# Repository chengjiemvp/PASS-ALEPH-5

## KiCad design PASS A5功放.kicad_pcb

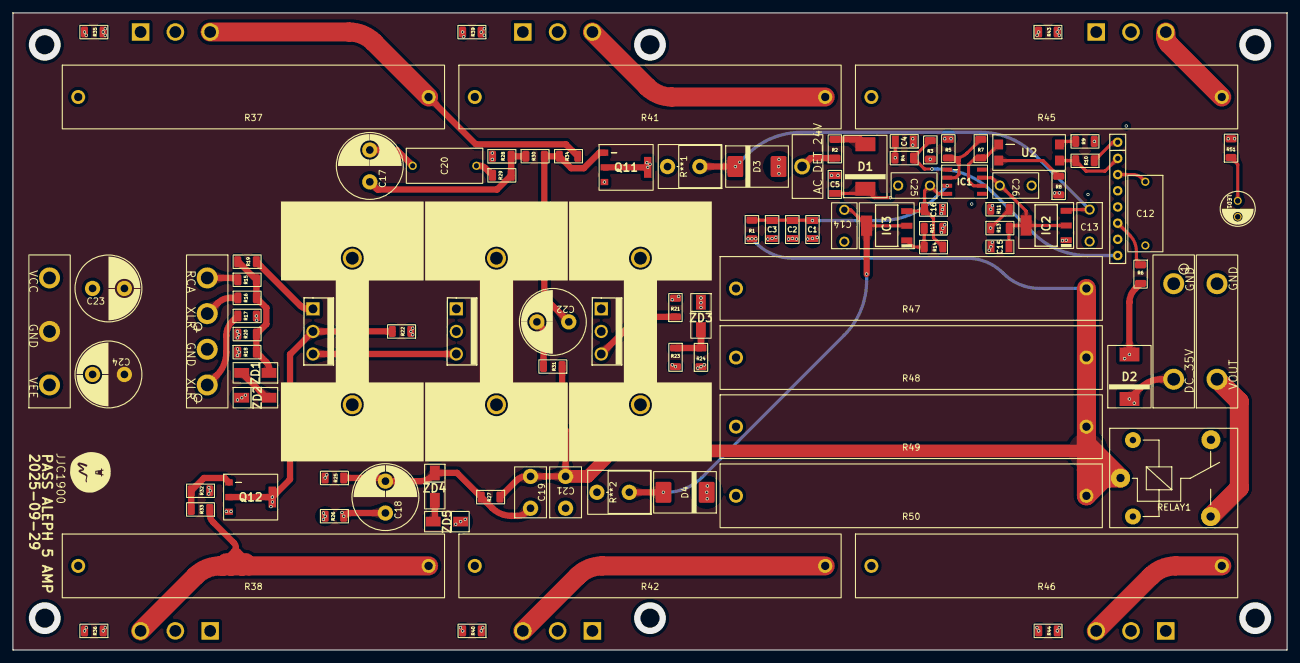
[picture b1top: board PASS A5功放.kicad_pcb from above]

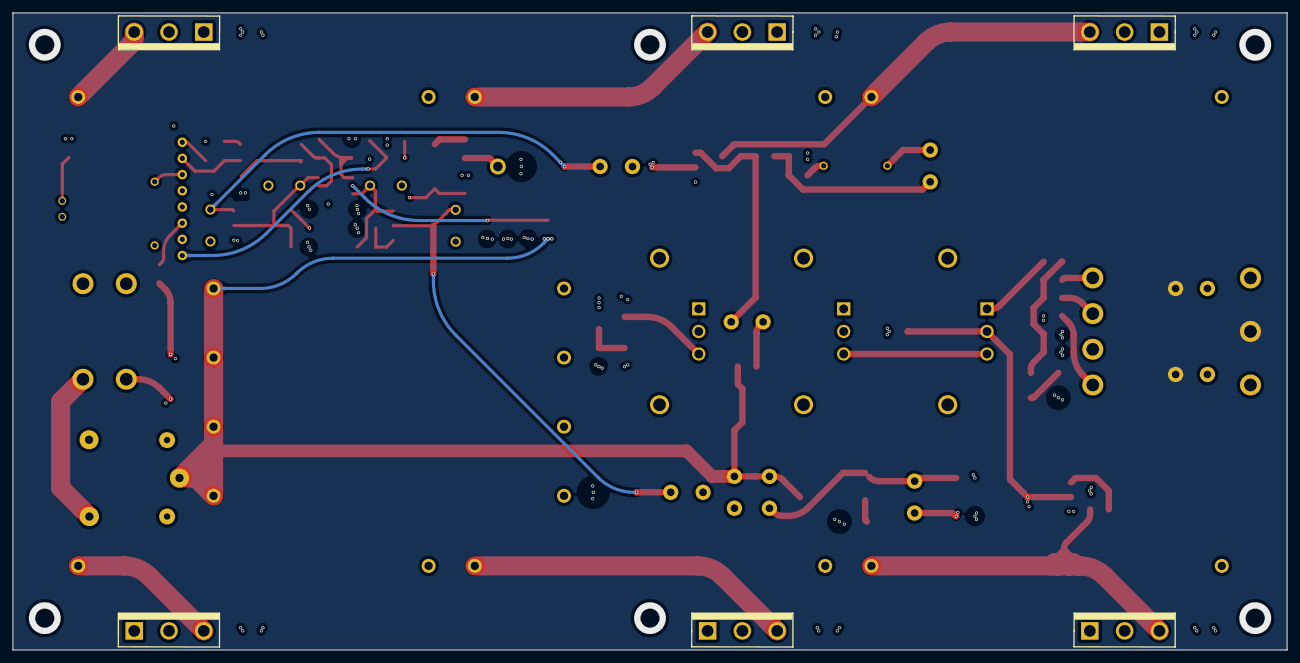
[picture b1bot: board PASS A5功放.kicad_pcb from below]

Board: 6 copper layers, 200.0 x 100.0 mm, 106 parts (6 on the bottom side), 61 nets.

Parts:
C1, C2, C3: 100μ; CGA1206X5R226M350NT
C4: 47μ; C3216X5R1E476MTJ00E
C5: 4.7μ; CL31B475KBHNNNE
C12: 22NF; KP223J2J1001
C13, C14, C25, C26: 0.1μ; MES104J2A-7-50R0
C15, C16: 22μ; CGA1206X5R226M350NT
C17, C18, C22: 220UF; SPZ1HM221G12O00RAXXX
C19: 10pF; CC45SL3FD100JYNNA
C20: 47nF; MPP473J2G10NN22610
C21: 680pF; CC3A681KC1GEB45F30MF
C23, C24: 470uF; SPZ1HM471G18O00RAXXX
CN1, CN3: 4线焊盘
CN2, CN4, CN5: 2线焊盘
D1, D2: S3M-E3/57T; S3M-E3_57T
D3, D4: SMC5352A
IC1: OPA1611AIDR
IC2: LM317AEMPX_NOPB
IC3: LM337IMP_NOPB
JJC***: LOGO
LED1: 20MA 3V; LED
Q1, Q2, Q3: IRF9610PBF
Q4, Q5, Q6, Q7, Q8, Q9: IRFP240PBF
Q11, Q12: BCP56-16,115
R1: 56K; R_1206
R2: 15K; R_1206
R3, R16, R17, R20, R24, R26, R51: 10K; R_1206
R4, R18, R27: 100K; R_1206
R5: 1000; R_1206
R6: 470; R_1206
R7: 3000; R_1206
R8: 500; R_1206
R9: 2000; R_1206
R10, R13, R14, R21, R35, R36, R39, R40, R43, R44: 220; R_1206
R11, R12: 887; R_1206
R15, R34: 1kΩ; R_1206
R19, R23, R25, R33: 220Ω; R_1206
R22: 390; R_1206
R28: 4.75K; R_1206
R29: 1.5K; R_1206
R30: 221K; R_1206
R31: 45K; R_1206
R32: 75; R_1206
R37, R38, R41, R42, R45, R46: 1; R 10W
R47, R48, R49, R50: .47; R 10W
R**1, R**2: 150; RSF5SSJT-73-150R_Vertical
RELAY1: G5LE-14 DC24; Relay_SPDT
U1: UPC1237HA
U2: SFH6206-2T
ZD1, ZD2, ZD3, ZD4, ZD5: SMAZ9V1-13-F

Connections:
/AC_DETECT: CN4.1 (AC_DET), R2.1
/DC 35V: CN2.1 (DC24V), D2.1 (K), R3.1, R9.2, RELAY1.2
/RCA: CN3.1 (RCA), R15.1
/UPC1237_PIN2: R10.2, U1.2, U2.3
/UPC1237_PIN4: C5.1, D1.1 (K), U1.4
/UPC1237_PIN7: C4.2, R4.1, U1.7
/UPC1237_PIN8: R3.2, R4.2, U1.8
/VCC: C23.1, CN1.1 (VCC), Q4.2 (D), Q6.2 (D), Q8.2 (D), R21.2, R28.2, R51.2, R**1.2, ZD3.1 (K)
/VCCO: C15.1, C26.2, IC1.7 (V+), IC2.2 (VOUT_1), IC2.4 (VOUT_2), R13.2
/VEE: C24.2, CN1.3 (VEE), Q3.2 (D), Q12.3 (E), R22.1, R32.1, R38.1, R42.1, R46.1, R**2.2
/VEEO: C16.2, C25.1, IC1.4 (V-), IC3.3 (VOUT), R14.1
/VIN: C19.2, C21.2, R1.1, R27.2, R31.1, R47.2, R48.2, R49.2, R50.2, RELAY1.1
/VOUT: CN5.1 (VOUT), RELAY1.3
/XLR_+: CN3.2 (XLR+), R16.1
/XLR_-: CN3.4 (XLR-), R17.1
GND: C1.2, C2.2, C3.2, C13.2, C14.1, C15.2, C16.1, C23.2, C24.1, C25.2, C26.1, CN1.2 (GND), CN3.3 (GND), CN5.2 (GND), D3.2 (A), D4.1 (K), R5.2, R8.1, R11.1, R12.2, R18.1, R20.1, R24.1, R26.1, ZD2.1 (K), ZD5.1 (K)
GND1: C4.1, C5.2, C12.2, CN2.2 (GND1), R10.1, U1.1, U1.5
unnamed: C12.1, U1.3
unnamed: C17.1, R28.1, R29.2, R30.1
unnamed: C18.1, R17.2, R26.2
unnamed: C22.2, R31.2
unnamed: D1.2 (A), R2.2
unnamed: D2.2 (A), R6.2, RELAY1.5
unnamed: C13.1, D3.1 (K), IC2.3 (VIN), R**1.1
unnamed: C14.2, D4.2 (A), IC3.2 (VIN_1), IC3.4 (VIN_2), R**2.1
unnamed: C1.1, C2.1, C3.1, IC1.3 (+IN), R1.2
unnamed: IC1.2 (-IN), R5.1, R7.2
unnamed: IC1.6 (OUT), R7.1, U2.1
unnamed: IC2.1 (ADJ), R11.2, R13.1
unnamed: IC3.1 (ADJ), R12.1, R14.2
unnamed: LED1.1 (A), R51.1
unnamed: C17.2, C20.1, LED1.2 (K), Q5.2 (D), Q7.2 (D), Q9.2 (D), Q11.3 (E), R37.1, R41.1, R45.1, R47.1, R48.1, R49.1, R50.1
unnamed: C21.1, Q1.2 (D), Q12.2 (C), R22.2, R36.2, R40.2, R44.2
unnamed: Q1.1 (G), R19.1
unnamed: Q1.3 (S), Q2.2 (D), Q3.3 (S)
unnamed: Q2.1 (G), R23.2
unnamed: Q2.3 (S), R21.1
unnamed: Q3.1 (G), R25.2
unnamed: Q4.1 (G), R35.1
unnamed: Q4.3 (S), R34.2, R37.2
unnamed: Q5.1 (G), R36.1
unnamed: Q5.3 (S), R33.1, R38.2
unnamed: Q6.1 (G), R39.1
unnamed: Q6.3 (S), R41.2
unnamed: Q7.1 (G), R40.1
unnamed: Q7.3 (S), R42.2
unnamed: Q8.1 (G), R43.1
unnamed: Q8.3 (S), R45.2
unnamed: Q9.1 (G), R44.1
unnamed: Q9.3 (S), R46.2
unnamed: C22.1, Q11.1 (B), R30.2, R34.1
unnamed: C20.2, Q11.2 (C), R29.1, R35.2, R39.2, R43.2
unnamed: Q12.1 (B), R32.2, R33.2
unnamed: R6.1, U1.6
unnamed: R8.2, U2.2
unnamed: R9.1, U2.4
unnamed: ZD1.2 (A), ZD2.2 (A)
unnamed: R15.2, R16.2, R18.2, R19.2, R20.2, ZD1.1 (K)
unnamed: R23.1, R24.2, ZD3.2 (A)
unnamed: ZD4.2 (A), ZD5.2 (A)
unnamed: C18.2, C19.1, R25.1, R27.1, ZD4.1 (K)

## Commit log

2025-09-30 6 layer-board
2025-10-01 using SMD power resistor
2025-10-07 fix some bugfs
2025-10-07 fix some bugs
2025-10-07 fix some bug
